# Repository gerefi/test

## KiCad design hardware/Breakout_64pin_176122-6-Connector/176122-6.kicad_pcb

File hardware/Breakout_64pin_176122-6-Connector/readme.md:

64 pin for Mazda Miata NA NB1

# [For sale here](https://www.tindie.com/products/russian/ecu-64p-connector-bare-pcb-honda-miata-nanb1/)

[Forum thread](https://gerefi.com/forum/viewtopic.php?f=4&t=507)

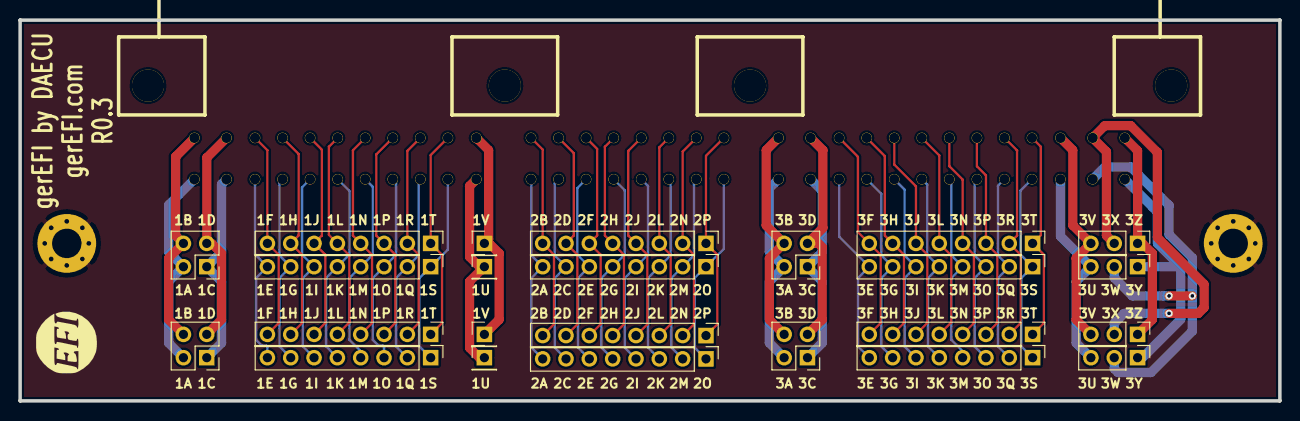
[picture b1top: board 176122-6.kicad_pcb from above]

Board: 2 copper layers, 137.2 x 41.5 mm, 28 parts (0 on the bottom side), 65 nets.

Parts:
G1: LOGO
H1, H2: MountingHole_Pad; MountingHole_3.2mm_M3_Pad_Via
P1, P2, P13, P14: CONN_3; PinHeader_1x03_P2.54mm_Vertical
P3, P4, P42, P43: Conn_01x04_Male; PinHeader_2x02_P2.54mm_Vertical
P7, P8, P19, P20: CONN_1; PinHeader_1x01_P2.54mm_Vertical
P25: 0176122-06; 176122-6
P26, P27, P28, P29, P30, P31, P32, P33, P34, P35, P36, P37: CONN_8; PinHeader_1x08_P2.54mm_Vertical

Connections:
GND: H1.1, H2.1
unnamed: P1.1, P13.1, P25.1
unnamed: P1.2, P13.2, P25.2
unnamed: P1.3, P13.3, P25.3
unnamed: P2.1, P14.1, P25.4
unnamed: P2.2, P14.2, P25.5
unnamed: P2.3, P14.3, P25.6
unnamed: P7.1, P19.1, P25.11
unnamed: P8.1, P20.1, P25.12
unnamed: P3.1, P4.1, P25.7
unnamed: P3.2, P4.2, P25.8
unnamed: P3.3, P4.3, P25.9
unnamed: P3.4, P4.4, P25.10
unnamed: P25.13, P42.1, P43.1
unnamed: P25.14, P42.2, P43.2
unnamed: P25.15, P42.3, P43.3
unnamed: P25.16, P42.4, P43.4
unnamed: P25.17, P26.1, P32.1
unnamed: P25.18, P26.2, P32.2
unnamed: P25.19, P26.3, P32.3
unnamed: P25.20, P26.4, P32.4
unnamed: P25.21, P26.5, P32.5
unnamed: P25.22, P26.6, P32.6
unnamed: P25.23, P26.7, P32.7
unnamed: P25.24, P26.8, P32.8
unnamed: P25.25, P27.1, P33.1
unnamed: P25.26, P27.2, P33.2
unnamed: P25.27, P27.3, P33.3
unnamed: P25.28, P27.4, P33.4
unnamed: P25.29, P27.5, P33.5
unnamed: P25.30, P27.6, P33.6
unnamed: P25.31, P27.7, P33.7
unnamed: P25.32, P27.8, P33.8
unnamed: P25.33, P28.1, P34.1
unnamed: P25.34, P28.2, P34.2
unnamed: P25.35, P28.3, P34.3
unnamed: P25.36, P28.4, P34.4
unnamed: P25.37, P28.5, P34.5
unnamed: P25.38, P28.6, P34.6
unnamed: P25.39, P28.7, P34.7
unnamed: P25.40, P28.8, P34.8
unnamed: P25.41, P29.1, P35.1
unnamed: P25.42, P29.2, P35.2
unnamed: P25.43, P29.3, P35.3
unnamed: P25.44, P29.4, P35.4
unnamed: P25.45, P29.5, P35.5
unnamed: P25.46, P29.6, P35.6
unnamed: P25.47, P29.7, P35.7
unnamed: P25.48, P29.8, P35.8
unnamed: P25.49, P30.1, P36.1
unnamed: P25.50, P30.2, P36.2
unnamed: P25.51, P30.3, P36.3
unnamed: P25.52, P30.4, P36.4
unnamed: P25.53, P30.5, P36.5
unnamed: P25.54, P30.6, P36.6
unnamed: P25.55, P30.7, P36.7
unnamed: P25.56, P30.8, P36.8
unnamed: P25.57, P31.1, P37.1
unnamed: P25.58, P31.2, P37.2
unnamed: P25.59, P31.3, P37.3
unnamed: P25.60, P31.4, P37.4
unnamed: P25.61, P31.5, P37.5
unnamed: P25.62, P31.6, P37.6
unnamed: P25.63, P31.7, P37.7
unnamed: P25.64, P31.8, P37.8

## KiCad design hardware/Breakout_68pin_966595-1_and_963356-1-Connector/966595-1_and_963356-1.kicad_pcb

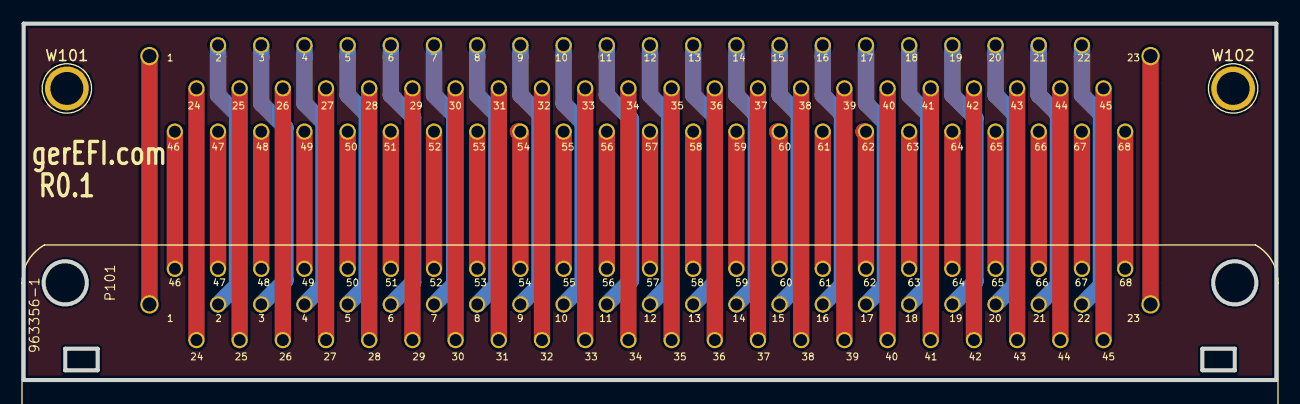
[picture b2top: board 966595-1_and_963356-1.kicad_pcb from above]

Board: 2 copper layers, 116.0 x 33.0 mm, 4 parts (1 on the bottom side), 69 nets.

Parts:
P101: 963356-1
P102: 966595-1
W101, W102: TEST_1P; 1pin

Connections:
GND: W101.1, W102.1
unnamed: P101.1, P102.1
unnamed: P101.2, P102.2
unnamed: P101.3, P102.3
unnamed: P101.4, P102.4
unnamed: P101.5, P102.5
unnamed: P101.6, P102.6
unnamed: P101.7, P102.7
unnamed: P101.8, P102.8
unnamed: P101.9, P102.9
unnamed: P101.10, P102.10
unnamed: P101.11, P102.11
unnamed: P101.12, P102.12
unnamed: P101.13, P102.13
unnamed: P101.14, P102.14
unnamed: P101.15, P102.15
unnamed: P101.16, P102.16
unnamed: P101.17, P102.17
unnamed: P101.18, P102.18
unnamed: P101.19, P102.19
unnamed: P101.20, P102.20
unnamed: P101.21, P102.21
unnamed: P101.22, P102.22
unnamed: P101.23, P102.23
unnamed: P101.24, P102.24
unnamed: P101.25, P102.25
unnamed: P101.26, P102.26
unnamed: P101.27, P102.27
unnamed: P101.28, P102.28
unnamed: P101.29, P102.29
unnamed: P101.30, P102.30
unnamed: P101.31, P102.31
unnamed: P101.32, P102.32
unnamed: P101.33, P102.33
unnamed: P101.34, P102.34
unnamed: P101.35, P102.35
unnamed: P101.36, P102.36
unnamed: P101.37, P102.37
unnamed: P101.38, P102.38
unnamed: P101.39, P102.39
unnamed: P101.40, P102.40
unnamed: P101.41, P102.41
unnamed: P101.42, P102.42
unnamed: P101.43, P102.43
unnamed: P101.44, P102.44
unnamed: P101.45, P102.45
unnamed: P101.46, P102.46
unnamed: P101.47, P102.47
unnamed: P101.48, P102.48
unnamed: P101.49, P102.49
unnamed: P101.50, P102.50
unnamed: P101.51, P102.51
unnamed: P101.52, P102.52
unnamed: P101.53, P102.53
unnamed: P101.54, P102.54
unnamed: P101.55, P102.55
unnamed: P101.56, P102.56
unnamed: P101.57, P102.57
unnamed: P101.58, P102.58
unnamed: P101.59, P102.59
unnamed: P101.60, P102.60
unnamed: P101.61, P102.61
unnamed: P101.62, P102.62
unnamed: P101.63, P102.63
unnamed: P101.64, P102.64
unnamed: P101.65, P102.65
unnamed: P101.66, P102.66
unnamed: P101.67, P102.67
unnamed: P101.68, P102.68

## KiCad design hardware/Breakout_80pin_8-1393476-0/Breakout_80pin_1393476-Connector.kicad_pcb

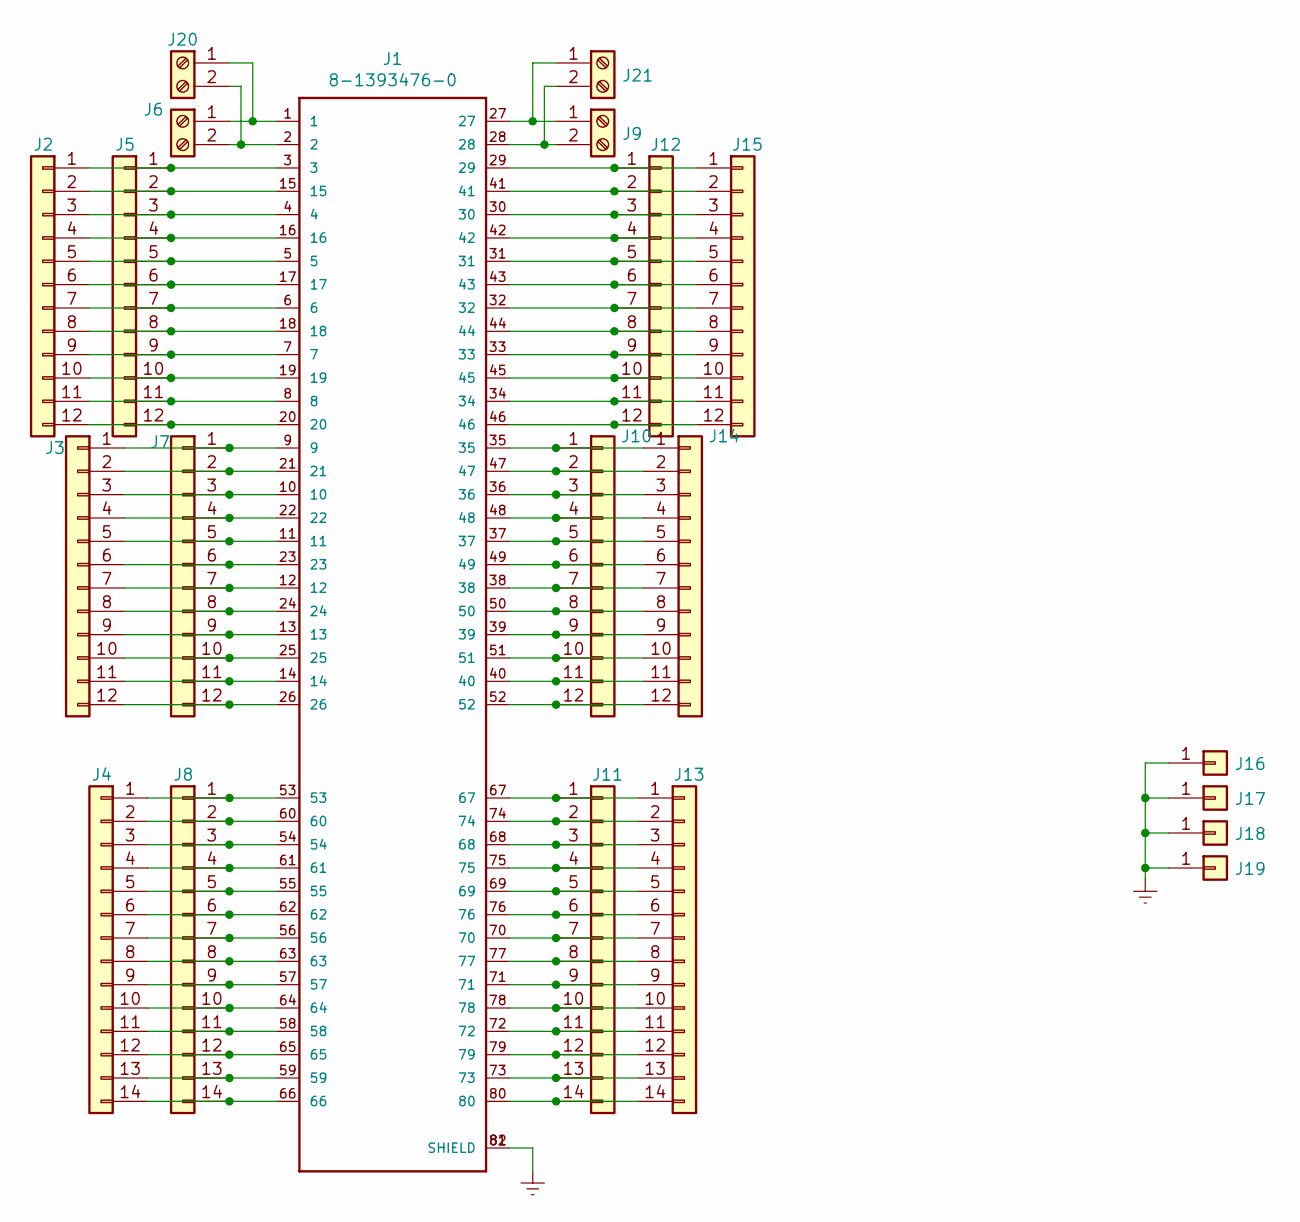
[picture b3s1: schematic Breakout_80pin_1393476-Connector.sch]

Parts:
J1: 8-1393476-0
J2, J3, J5, J7, J10, J12, J14, J15: Conn_01x12; Pin_Header_Straight_1x12_Pitch2.54mm
J4, J8, J11, J13: Conn_01x14; Pin_Header_Straight_1x14_Pitch2.54mm
J6, J9, J20, J21: Screw_Terminal_01x02; WireConnection_2.50mmDrill
J16, J17, J18, J19: Conn_01x01; Pin_Header_Straight_1x01_Pitch2.54mm

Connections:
Earth: J1.81 (SHIELD), J1.82 (SHIELD), J16.1, J17.1, J18.1, J19.1
unnamed: J1.1, J6.1, J20.1
unnamed: J1.2, J6.2, J20.2
unnamed: J1.3, J2.1, J5.1
unnamed: J1.4, J2.3, J5.3
unnamed: J1.5, J2.5, J5.5
unnamed: J1.6, J2.7, J5.7
unnamed: J1.7, J2.9, J5.9
unnamed: J1.8, J2.11, J5.11
unnamed: J1.9, J3.1, J7.1
unnamed: J1.10, J3.3, J7.3
unnamed: J1.11, J3.5, J7.5
unnamed: J1.12, J3.7, J7.7
unnamed: J1.13, J3.9, J7.9
unnamed: J1.14, J3.11, J7.11
unnamed: J1.15, J2.2, J5.2
unnamed: J1.16, J2.4, J5.4
unnamed: J1.17, J2.6, J5.6
unnamed: J1.18, J2.8, J5.8
unnamed: J1.19, J2.10, J5.10
unnamed: J1.20, J2.12, J5.12
unnamed: J1.21, J3.2, J7.2
unnamed: J1.22, J3.4, J7.4
unnamed: J1.23, J3.6, J7.6
unnamed: J1.24, J3.8, J7.8
unnamed: J1.25, J3.10, J7.10
unnamed: J1.26, J3.12, J7.12
unnamed: J1.27, J9.1, J21.1
unnamed: J1.28, J9.2, J21.2
unnamed: J1.29, J12.1, J15.1
unnamed: J1.30, J12.3, J15.3
unnamed: J1.31, J12.5, J15.5
unnamed: J1.32, J12.7, J15.7
unnamed: J1.33, J12.9, J15.9
unnamed: J1.34, J12.11, J15.11
unnamed: J1.35, J10.1, J14.1
unnamed: J1.36, J10.3, J14.3
unnamed: J1.37, J10.5, J14.5
unnamed: J1.38, J10.7, J14.7
unnamed: J1.39, J10.9, J14.9
unnamed: J1.40, J10.11, J14.11
unnamed: J1.41, J12.2, J15.2
unnamed: J1.42, J12.4, J15.4
unnamed: J1.43, J12.6, J15.6
unnamed: J1.44, J12.8, J15.8
unnamed: J1.45, J12.10, J15.10
unnamed: J1.46, J12.12, J15.12
unnamed: J1.47, J10.2, J14.2
unnamed: J1.48, J10.4, J14.4
unnamed: J1.49, J10.6, J14.6
unnamed: J1.50, J10.8, J14.8
unnamed: J1.51, J10.10, J14.10
unnamed: J1.52, J10.12, J14.12
unnamed: J1.53, J4.1, J8.1
unnamed: J1.54, J4.3, J8.3
unnamed: J1.55, J4.5, J8.5
unnamed: J1.56, J4.7, J8.7
unnamed: J1.57, J4.9, J8.9
unnamed: J1.58, J4.11, J8.11
unnamed: J1.59, J4.13, J8.13
unnamed: J1.60, J4.2, J8.2
unnamed: J1.61, J4.4, J8.4
unnamed: J1.62, J4.6, J8.6
unnamed: J1.63, J4.8, J8.8
unnamed: J1.64, J4.10, J8.10
unnamed: J1.65, J4.12, J8.12
unnamed: J1.66, J4.14, J8.14
unnamed: J1.67, J11.1, J13.1
unnamed: J1.68, J11.3, J13.3
unnamed: J1.69, J11.5, J13.5
unnamed: J1.70, J11.7, J13.7
unnamed: J1.71, J11.9, J13.9
unnamed: J1.72, J11.11, J13.11
unnamed: J1.73, J11.13, J13.13
unnamed: J1.74, J11.2, J13.2
unnamed: J1.75, J11.4, J13.4
unnamed: J1.76, J11.6, J13.6
unnamed: J1.77, J11.8, J13.8
unnamed: J1.78, J11.10, J13.10
unnamed: J1.79, J11.12, J13.12
unnamed: J1.80, J11.14, J13.14

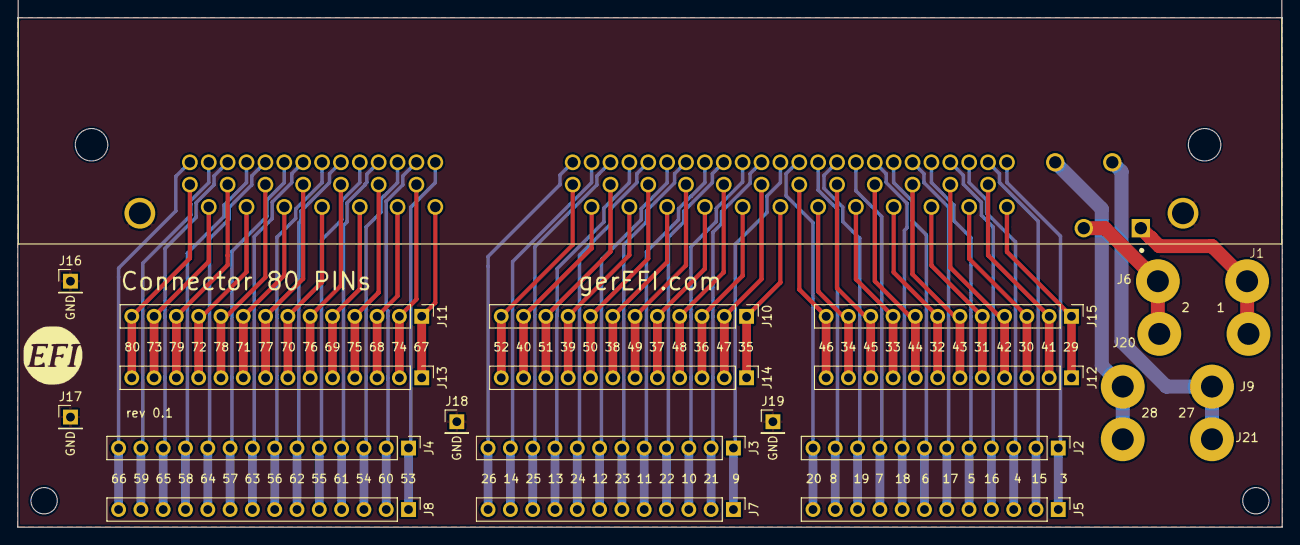
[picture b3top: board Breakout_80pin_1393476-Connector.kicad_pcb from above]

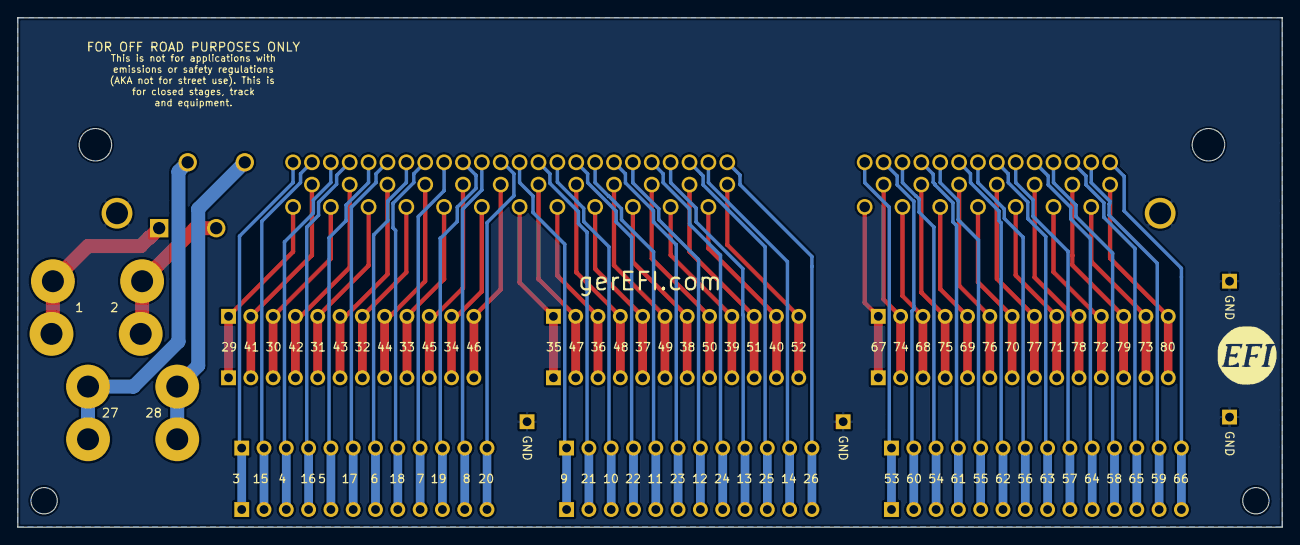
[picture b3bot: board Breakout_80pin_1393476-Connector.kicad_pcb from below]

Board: 2 copper layers, 144.0 x 58.0 mm, 24 parts (2 on the bottom side), 81 nets.

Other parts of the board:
G?: Disclaimer; Off_Road_Disclaimer
G?#2, G?#3: LOGO

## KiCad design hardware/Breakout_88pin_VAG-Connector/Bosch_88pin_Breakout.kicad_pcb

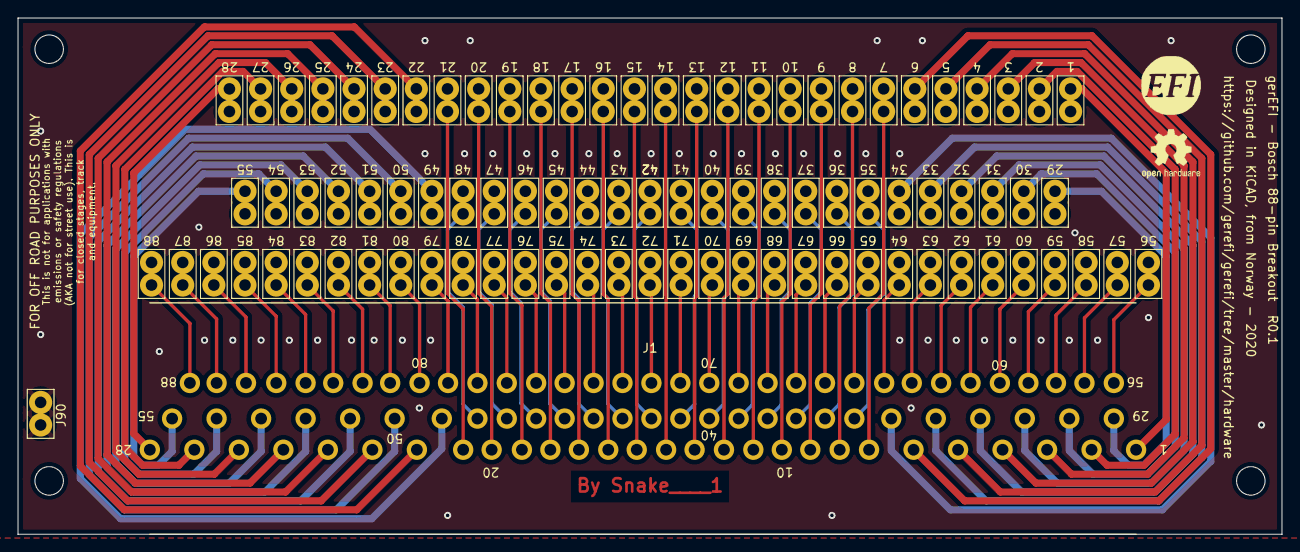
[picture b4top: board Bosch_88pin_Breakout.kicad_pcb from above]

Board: 2 copper layers, 142.0 x 58.0 mm, 97 parts (0 on the bottom side), 88 nets.

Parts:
G1: LOGO
G2: Disclaimer; Off_Road_Disclaimer
H1, H2, H3, H4: M3; MountingHole_3.2mm_M3_DIN965
J1: BOSCH_88PIN_02X44; BOSCH-88pin
J2: Pin1; TestPoint_Bridge_Pitch2.54mm_Drill1.3mm
J3: Pin3; TestPoint_Bridge_Pitch2.54mm_Drill1.3mm
J4: Pin5; TestPoint_Bridge_Pitch2.54mm_Drill1.3mm
J5: Pin7; TestPoint_Bridge_Pitch2.54mm_Drill1.3mm
J6: Pin9; TestPoint_Bridge_Pitch2.54mm_Drill1.3mm
J7: Pin11; TestPoint_Bridge_Pitch2.54mm_Drill1.3mm
J8: Pin13; TestPoint_Bridge_Pitch2.54mm_Drill1.3mm
J9: Pin15; TestPoint_Bridge_Pitch2.54mm_Drill1.3mm
J10: Pin17; TestPoint_Bridge_Pitch2.54mm_Drill1.3mm
J11: Pin19; TestPoint_Bridge_Pitch2.54mm_Drill1.3mm
J12: Pin21; TestPoint_Bridge_Pitch2.54mm_Drill1.3mm
J13: Pin23; TestPoint_Bridge_Pitch2.54mm_Drill1.3mm
J14: Pin25; TestPoint_Bridge_Pitch2.54mm_Drill1.3mm
J15: Pin27; TestPoint_Bridge_Pitch2.54mm_Drill1.3mm
J16: Pin29; TestPoint_Bridge_Pitch2.54mm_Drill1.3mm
J17: Pin31; TestPoint_Bridge_Pitch2.54mm_Drill1.3mm
J18: Pin33; TestPoint_Bridge_Pitch2.54mm_Drill1.3mm
J19: Pin35; TestPoint_Bridge_Pitch2.54mm_Drill1.3mm
J20: Pin37; TestPoint_Bridge_Pitch2.54mm_Drill1.3mm
J21: Pin39; TestPoint_Bridge_Pitch2.54mm_Drill1.3mm
J22: Pin41; TestPoint_Bridge_Pitch2.54mm_Drill1.3mm
J23: Pin43; TestPoint_Bridge_Pitch2.54mm_Drill1.3mm
J24: Pin45; TestPoint_Bridge_Pitch2.54mm_Drill1.3mm
J25: Pin47; TestPoint_Bridge_Pitch2.54mm_Drill1.3mm
J26: Pin49; TestPoint_Bridge_Pitch2.54mm_Drill1.3mm
J27: Pin51; TestPoint_Bridge_Pitch2.54mm_Drill1.3mm
J28: Pin53; TestPoint_Bridge_Pitch2.54mm_Drill1.3mm
J29: Pin55; TestPoint_Bridge_Pitch2.54mm_Drill1.3mm
J30: Pin57; TestPoint_Bridge_Pitch2.54mm_Drill1.3mm
J31: Pin59; TestPoint_Bridge_Pitch2.54mm_Drill1.3mm
J32: Pin61; TestPoint_Bridge_Pitch2.54mm_Drill1.3mm
J33: Pin63; TestPoint_Bridge_Pitch2.54mm_Drill1.3mm
J34: Pin65; TestPoint_Bridge_Pitch2.54mm_Drill1.3mm
J35: Pin67; TestPoint_Bridge_Pitch2.54mm_Drill1.3mm
J36: Pin69; TestPoint_Bridge_Pitch2.54mm_Drill1.3mm
J37: Pin71; TestPoint_Bridge_Pitch2.54mm_Drill1.3mm
J38: Pin73; TestPoint_Bridge_Pitch2.54mm_Drill1.3mm
J39: Pin75; TestPoint_Bridge_Pitch2.54mm_Drill1.3mm
J40: Pin77; TestPoint_Bridge_Pitch2.54mm_Drill1.3mm
J41: Pin79; TestPoint_Bridge_Pitch2.54mm_Drill1.3mm
J42: Pin81; TestPoint_Bridge_Pitch2.54mm_Drill1.3mm
J43: Pin83; TestPoint_Bridge_Pitch2.54mm_Drill1.3mm
J44: Pin85; TestPoint_Bridge_Pitch2.54mm_Drill1.3mm
J45: Pin87; TestPoint_Bridge_Pitch2.54mm_Drill1.3mm
J46: Pin2; TestPoint_Bridge_Pitch2.54mm_Drill1.3mm
J47: Pin4; TestPoint_Bridge_Pitch2.54mm_Drill1.3mm
J48: Pin6; TestPoint_Bridge_Pitch2.54mm_Drill1.3mm
J49: Pin8; TestPoint_Bridge_Pitch2.54mm_Drill1.3mm
J50: Pin10; TestPoint_Bridge_Pitch2.54mm_Drill1.3mm
J51: Pin12; TestPoint_Bridge_Pitch2.54mm_Drill1.3mm
J52: Pin14; TestPoint_Bridge_Pitch2.54mm_Drill1.3mm
J53: Pin16; TestPoint_Bridge_Pitch2.54mm_Drill1.3mm
J54: Pin18; TestPoint_Bridge_Pitch2.54mm_Drill1.3mm
J55: Pin20; TestPoint_Bridge_Pitch2.54mm_Drill1.3mm
J56: Pin22; TestPoint_Bridge_Pitch2.54mm_Drill1.3mm
J57: Pin24; TestPoint_Bridge_Pitch2.54mm_Drill1.3mm
J58: Pin26; TestPoint_Bridge_Pitch2.54mm_Drill1.3mm
J59: Pin28; TestPoint_Bridge_Pitch2.54mm_Drill1.3mm
J60: Pin30; TestPoint_Bridge_Pitch2.54mm_Drill1.3mm
J61: Pin32; TestPoint_Bridge_Pitch2.54mm_Drill1.3mm
J62: Pin34; TestPoint_Bridge_Pitch2.54mm_Drill1.3mm
J63: Pin36; TestPoint_Bridge_Pitch2.54mm_Drill1.3mm
J64: Pin38; TestPoint_Bridge_Pitch2.54mm_Drill1.3mm
J65: Pin40; TestPoint_Bridge_Pitch2.54mm_Drill1.3mm
J66: Pin42; TestPoint_Bridge_Pitch2.54mm_Drill1.3mm
J67: Pin44; TestPoint_Bridge_Pitch2.54mm_Drill1.3mm
J68: Pin46; TestPoint_Bridge_Pitch2.54mm_Drill1.3mm
J69: Pin48; TestPoint_Bridge_Pitch2.54mm_Drill1.3mm
J70: Pin50; TestPoint_Bridge_Pitch2.54mm_Drill1.3mm
J71: Pin52; TestPoint_Bridge_Pitch2.54mm_Drill1.3mm
J72: Pin54; TestPoint_Bridge_Pitch2.54mm_Drill1.3mm
J73: Pin56; TestPoint_Bridge_Pitch2.54mm_Drill1.3mm
J74: Pin58; TestPoint_Bridge_Pitch2.54mm_Drill1.3mm
J75: Pin60; TestPoint_Bridge_Pitch2.54mm_Drill1.3mm
J76: Pin62; TestPoint_Bridge_Pitch2.54mm_Drill1.3mm
J77: Pin64; TestPoint_Bridge_Pitch2.54mm_Drill1.3mm
J78: Pin66; TestPoint_Bridge_Pitch2.54mm_Drill1.3mm
J79: Pin68; TestPoint_Bridge_Pitch2.54mm_Drill1.3mm
J80: Pin70; TestPoint_Bridge_Pitch2.54mm_Drill1.3mm
J81: Pin72; TestPoint_Bridge_Pitch2.54mm_Drill1.3mm
J82: Pin74; TestPoint_Bridge_Pitch2.54mm_Drill1.3mm
J83: Pin76; TestPoint_Bridge_Pitch2.54mm_Drill1.3mm
J84: Pin78; TestPoint_Bridge_Pitch2.54mm_Drill1.3mm
J85: Pin80; TestPoint_Bridge_Pitch2.54mm_Drill1.3mm
J86: Pin82; TestPoint_Bridge_Pitch2.54mm_Drill1.3mm
J87: Pin84; TestPoint_Bridge_Pitch2.54mm_Drill1.3mm
J88: Pin86; TestPoint_Bridge_Pitch2.54mm_Drill1.3mm
J89: Pin88; TestPoint_Bridge_Pitch2.54mm_Drill1.3mm
J90: GND; TestPoint_Bridge_Pitch2.54mm_Drill1.3mm
LOGO1: Logo_Open_Hardware_Small; OSHW-Logo2_7.3x6mm_SilkScreen

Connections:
unnamed: J1.1, J2.1
unnamed: J1.2, J46.1
unnamed: J1.3, J3.1
unnamed: J1.4, J47.1
unnamed: J1.5, J4.1
unnamed: J1.6, J48.1
unnamed: J1.7, J5.1
unnamed: J1.8, J49.1
unnamed: J1.9, J6.1
unnamed: J1.10, J50.1
unnamed: J1.11, J7.1
unnamed: J1.12, J51.1
unnamed: J1.13, J8.1
unnamed: J1.14, J52.1
unnamed: J1.15, J9.1
unnamed: J1.16, J53.1
unnamed: J1.17, J10.1
unnamed: J1.18, J54.1
unnamed: J1.19, J11.1
unnamed: J1.20, J55.1
unnamed: J1.21, J12.1
unnamed: J1.22, J56.1
unnamed: J1.23, J13.1
unnamed: J1.24, J57.1
unnamed: J1.25, J14.1
unnamed: J1.26, J58.1
unnamed: J1.27, J15.1
unnamed: J1.28, J59.1
unnamed: J1.29, J16.1
unnamed: J1.30, J60.1
unnamed: J1.31, J17.1
unnamed: J1.32, J61.1
unnamed: J1.33, J18.1
unnamed: J1.34, J62.1
unnamed: J1.35, J19.1
unnamed: J1.36, J63.1
unnamed: J1.37, J20.1
unnamed: J1.38, J64.1
unnamed: J1.39, J21.1
unnamed: J1.40, J65.1
unnamed: J1.41, J22.1
unnamed: J1.42, J66.1
unnamed: J1.43, J23.1
unnamed: J1.44, J67.1
unnamed: J1.45, J24.1
unnamed: J1.46, J68.1
unnamed: J1.47, J25.1
unnamed: J1.48, J69.1
unnamed: J1.49, J26.1
unnamed: J1.50, J70.1
unnamed: J1.51, J27.1
unnamed: J1.52, J71.1
unnamed: J1.53, J28.1
unnamed: J1.54, J72.1
unnamed: J1.55, J29.1
unnamed: J1.56, J73.1
unnamed: J1.57, J30.1
unnamed: J1.58, J74.1
unnamed: J1.59, J31.1
unnamed: J1.60, J75.1
unnamed: J1.61, J32.1
unnamed: J1.62, J76.1
unnamed: J1.63, J33.1
unnamed: J1.64, J77.1
unnamed: J1.65, J34.1
unnamed: J1.66, J78.1
unnamed: J1.67, J35.1
unnamed: J1.68, J79.1
unnamed: J1.69, J36.1
unnamed: J1.70, J80.1
unnamed: J1.71, J37.1
unnamed: J1.72, J81.1
unnamed: J1.73, J38.1
unnamed: J1.74, J82.1
unnamed: J1.75, J39.1
unnamed: J1.76, J83.1
unnamed: J1.77, J40.1
unnamed: J1.78, J84.1
unnamed: J1.79, J41.1
unnamed: J1.80, J85.1
unnamed: J1.81, J42.1
unnamed: J1.82, J86.1
unnamed: J1.83, J43.1
unnamed: J1.84, J87.1
unnamed: J1.85, J44.1
unnamed: J1.86, J88.1
unnamed: J1.87, J45.1
unnamed: J1.88, J89.1

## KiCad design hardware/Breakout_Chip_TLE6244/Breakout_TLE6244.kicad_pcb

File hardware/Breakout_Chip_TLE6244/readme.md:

https://gerefi.com/forum/viewtopic.php?f=4&t=577

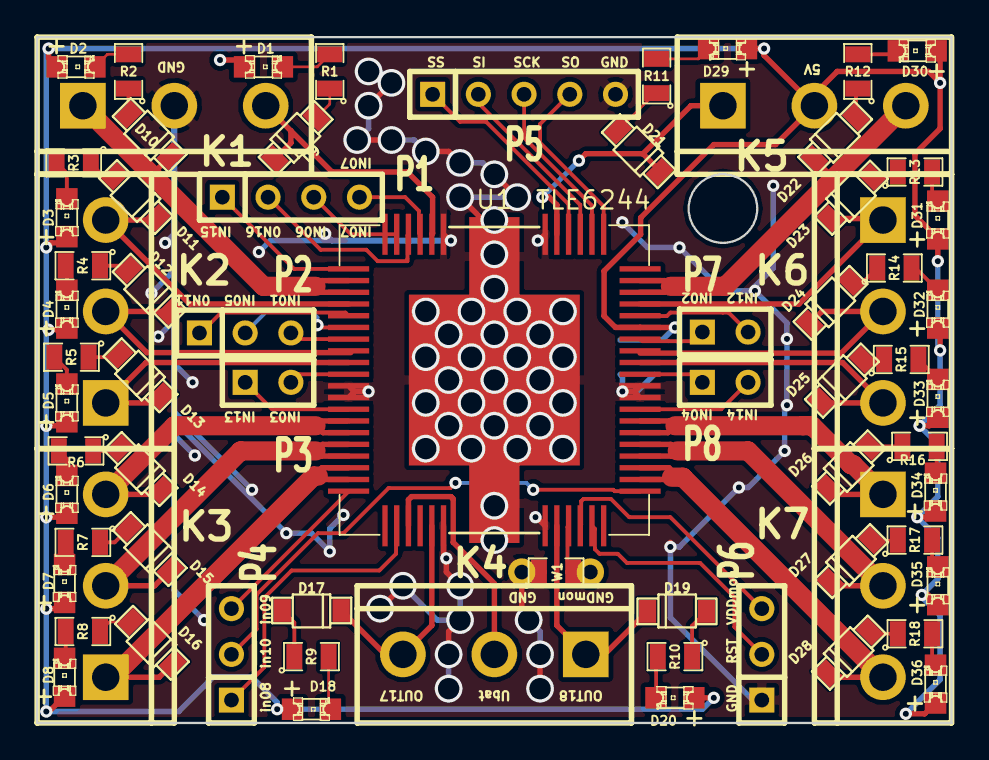
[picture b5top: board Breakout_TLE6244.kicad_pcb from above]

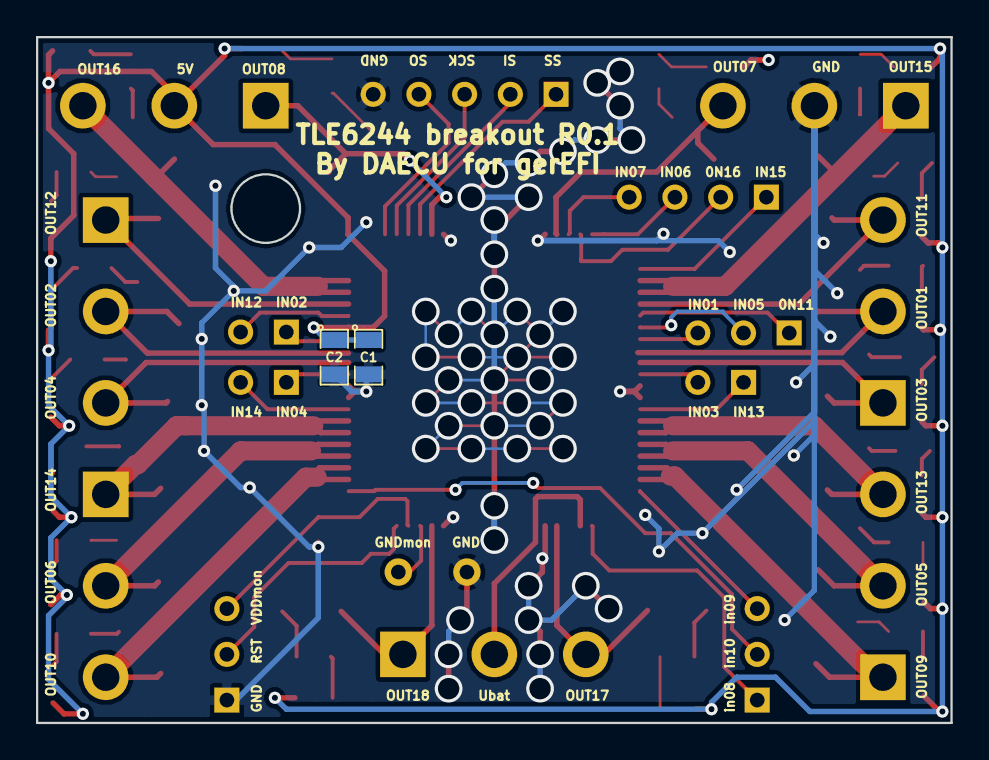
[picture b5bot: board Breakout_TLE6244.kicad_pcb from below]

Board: 4 copper layers, 50.8 x 38.1 mm, 73 parts (2 on the bottom side), 80 nets.

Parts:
C1: 1uF; SM0805
C2: .01uF; SM0805
D1, D2, D3, D4, D5, D6, D7, D8, D18, D20, D29, D30, D31, D32, D33, D34, D35, D36: LED-red; LED-0805_A
D9, D10, D11, D12, D13, D14, D15, D16, D17, D19, D21, D22, D23, D24, D25, D26, D27, D28: DIODE; SOD-123
K1, K2, K3, K4, K5, K6, K7: CONN_3; bornier3
P1: CONN_4; SIL-4
P2, P4, P6: CONN_3; SIL-3
P3, P7, P8: CONN_2; SIL-2
P5: CONN_5; SIL-5
R1, R2, R3, R4, R5, R6, R7, R8, R9, R10, R11, R12, R13, R14, R15, R16, R17, R18: 1K; SM0805
U1: TLE6244; HiQUAD64
W1: TEST; SM0805_jumper

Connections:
/5v: C1.1, C2.1, D1.1, D2.1, D3.1, D4.1, D5.1, D6.1, D7.1, D8.1, D18.1, D20.1, D29.1, D30.1, D31.1, D32.1, D33.1, D34.1, D35.1, D36.1, K5.2, U1.47
/GNDmon: U1.29, W1.2
/RST: P6.2, U1.31
/SCK: P5.3, U1.54
/SI: P5.2, U1.55
/SO: P5.4, U1.53
/SS: P5.1, U1.56
/Ubatt: K4.2, U1.23
/VDDmon: P6.3, U1.30
/in01: P2.3, U1.7
/in02: P7.1, U1.46
/in03: P3.2, U1.10
/in04: P8.1, U1.43
/in05: P2.2, U1.6
/in06: P1.3, U1.63, U1.64
/in07: P1.4, U1.61
/in08: P4.1, U1.22
/in09: P4.3, U1.20
/in10: P4.2, U1.33
/in11: P2.1, U1.5
/in12: P7.2, U1.48
/in13: P3.1, U1.13
/in14: P8.2, U1.40
/in15: P1.1, U1.1
/in16: P1.2, U1.62
/out01: D12.2, K2.2, U1.8
/out02: D24.2, K6.2, U1.45
/out03: D13.2, K2.1, U1.9
/out04: D25.2, K6.3, U1.44
/out05: D15.2, K3.2, U1.16, U1.17
/out06: D27.2, K7.2, U1.36, U1.37
/out07: D9.2, K1.3, U1.60
/out08: D21.2, K5.1, U1.57
/out09: D16.2, K3.1, U1.18, U1.19
/out10: D28.2, K7.3, U1.34, U1.35
/out11: D11.2, K2.3, U1.4
/out12: D23.2, K6.1, U1.49
/out13: D14.2, K3.3, U1.14, U1.15
/out14: D26.2, K7.1, U1.38, U1.39
/out15: D10.2, K1.1, U1.2, U1.3
/out16: D22.2, K5.3, U1.50, U1.51
/out17: D17.2, K4.3, U1.25
/out18: D19.2, K4.1, U1.28
GND: C1.2, C2.2, K1.2, P5.5, P6.1, U1.11, U1.12, U1.26, U1.27, U1.41, U1.42, U1.58, U1.59, U1.slug, W1.1
unnamed: D9.1, R1.1
unnamed: D21.1, R11.1
unnamed: D29.2, R11.2
unnamed: D1.2, R1.2
unnamed: D17.1, R9.1
unnamed: D18.2, R9.2
unnamed: D3.2, R3.2
unnamed: D11.1, R3.1
unnamed: D22.1, R12.1
unnamed: D30.2, R12.2
unnamed: D2.2, R2.2
unnamed: D10.1, R2.1
unnamed: D27.1, R17.1
unnamed: D28.1, R18.1
unnamed: D36.2, R18.2
unnamed: D35.2, R17.2
unnamed: D26.1, R16.1
unnamed: D34.2, R16.2
unnamed: D25.1, R15.1
unnamed: D33.2, R15.2
unnamed: D19.1, R10.1
unnamed: D20.2, R10.2
unnamed: D5.2, R5.2
unnamed: D7.2, R7.2
unnamed: D15.1, R7.1
unnamed: D14.1, R6.1
unnamed: D6.2, R6.2
unnamed: D13.1, R5.1
unnamed: D12.1, R4.1
unnamed: D4.2, R4.2
unnamed: D24.1, R14.1
unnamed: D32.2, R14.2
unnamed: D23.1, R13.1
unnamed: D31.2, R13.2
unnamed: D16.1, R8.1
unnamed: D8.2, R8.2
